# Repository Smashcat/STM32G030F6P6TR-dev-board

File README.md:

# STM32G030F6P6TR development board
Small breadboard friendly development board for the 32bit STM32G030F6P6TR microcontroller (currently stocked and priced at just over $1 on JLC!) with the following available features:

- 32Kb Flash
- 8Kb RAM.
- 12 bit ADC (16 channels)
- 2 x USART
- 2 x i2C
- i2S
- 2 x SPI
- 17 x GPIOs
- 5 DMA channels for above peripherals, plus memory to memory transfers
- Realtime clock with calendar and alarm with interrupt generation
- 8 x timers
- 2 x watchdogs

Note that many of the peripherals share pins.

This board includes 8 USER LEDs, 2 user buttons, UART to USB bridge, SHT30-DIS-B temperature and humidity sensor and all pins broken out for development use. Pullups on i2C pins. On-board 3.3V regulator from USB supply, with header pins for 3.3V and 5V available for use.

The V1.1 version also includes a LSM6DS3TR IMU device on the i2C bus. Other than this, it is identical.

All files required for full PCBA production at JLCPCB are included in the "Production files" folder.

Example firmware added to show use of i2C sensor, plus LEDs and internal clock.

V1.0

V1.1 (with IMU)

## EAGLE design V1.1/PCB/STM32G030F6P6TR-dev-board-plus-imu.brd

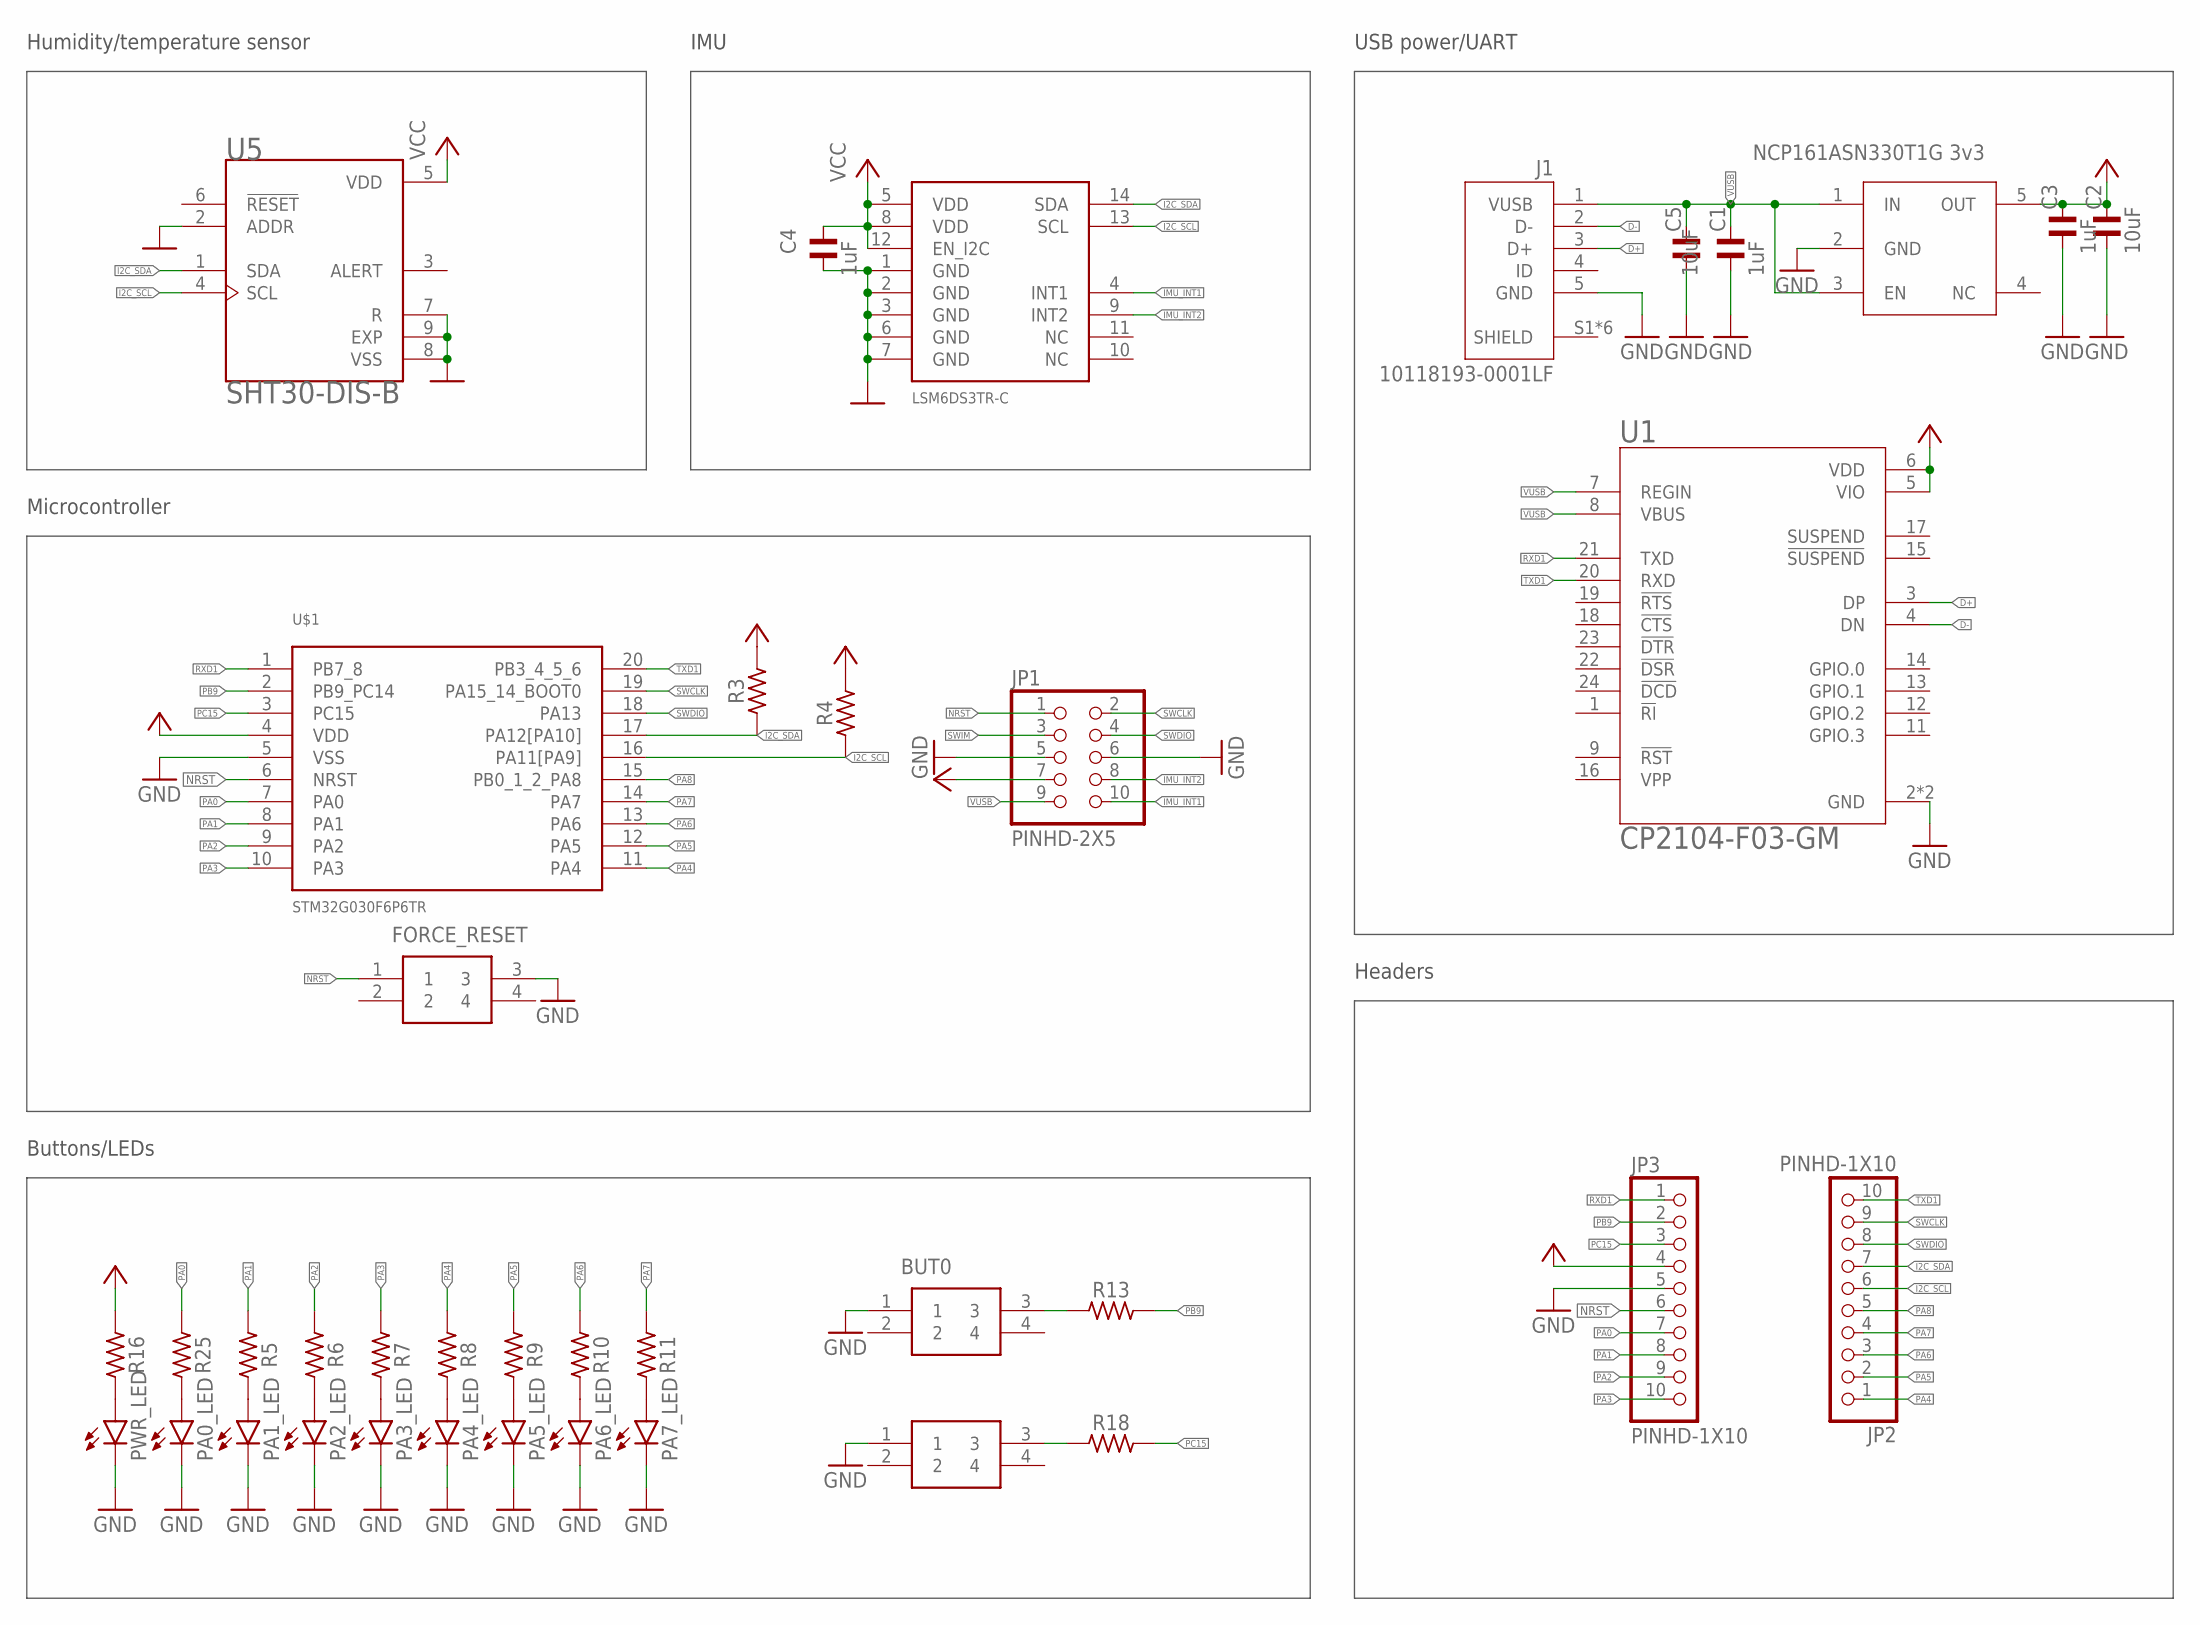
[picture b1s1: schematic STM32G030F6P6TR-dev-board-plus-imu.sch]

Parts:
3V3_REG1: 3V3; NCP718BSN330T1G
BUT0, BUT1: PTS645SM43SMTR92LFS; PTS645(SMT)
C1, C3, C4: 1uF; RC-MASTER-SMD_C0603MP
C2, C5: 10uF; RC-MASTER-SMD_C0603MP
FORCE_RESET: PTS645SM43SMTR92LFS; PTS645(SMT)
J1: 10118193-0001LF; FCI_10118193-0001LF
JP1: PINHD-2X5; 2X05
JP2, JP3: PINHD-1X10; 1X10
PA0_LED, PA1_LED, PA2_LED, PA3_LED, PA4_LED, PA5_LED, PA6_LED, PA7_LED: 20mA; CHIP-LED0603
PWR_LED: 20mA; CHIP-LED0603
R3, R4: 3k3; 52101-101-REV-A_RC-MASTER-SMD_R0603MP
R5, R6, R7, R8, R9, R10, R11, R16, R25: 1K; 52101-101-REV-A_RC-MASTER-SMD_R0603MP
R13, R18: 100R; 52101-101-REV-A_RC-MASTER-SMD_R0603MP
U1: CP2104-F03-GM; QFN50P400X400X80-25N
U5: SHT30-DIS-B; DFN250X250X100-9N
U$1: STM32G030F6P6TR; SOP65P640X120-20N
U$2: LSM6DS3TR-IMU; LSM6DS3TR

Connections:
D+: J1.3 (D+), U1.3 (DP)
D-: J1.2 (D-), U1.4 (DN)
GND: 3V3_REG1.2 (GND), BUT0.1, BUT1.1, C1.1, C2.1, C3.1, C4.1, C5.1, FORCE_RESET.3, J1.5 (GND), JP1.5, JP1.6, JP3.5, PA0_LED.C, PA1_LED.C, PA2_LED.C, PA3_LED.C, PA4_LED.C, PA5_LED.C, PA6_LED.C, PA7_LED.C, PWR_LED.C, U1.2 (GND), U1.25 (GND), U5.2 (ADDR), U5.7 (R), U5.8 (VSS), U5.9 (EXP), U$1.5 (VSS), U$2.1 (GND), U$2.2 (GND), U$2.3 (GND), U$2.6 (GND), U$2.7 (GND)
I2C_SCL: JP2.6, R4.2, U5.4 (SCL), U$1.16 (PA11[PA9]), U$2.13 (SCL)
I2C_SDA: JP2.7, R3.2, U5.1 (SDA), U$1.17 (PA12[PA10]), U$2.14 (SDA)
IMU_INT1: JP1.10, U$2.4 (INT1)
IMU_INT2: JP1.8, U$2.9 (INT2)
unnamed: PA1_LED.A, R5.1
unnamed: PA2_LED.A, R6.1
unnamed: PA0_LED.A, R25.1
unnamed: PA3_LED.A, R7.1
unnamed: PA4_LED.A, R8.1
unnamed: PA5_LED.A, R9.1
unnamed: PA6_LED.A, R10.1
unnamed: PA7_LED.A, R11.1
unnamed: BUT0.3, R13.2
unnamed: PWR_LED.A, R16.1
unnamed: BUT1.3, R18.2
NRST: FORCE_RESET.1, JP1.1, JP3.6, U$1.6 (NRST)
PA0: JP3.7, R25.2, U$1.7 (PA0)
PA1: JP3.8, R5.2, U$1.8 (PA1)
PA2: JP3.9, R6.2, U$1.9 (PA2)
PA3: JP3.10, R7.2, U$1.10 (PA3)
PA4: JP2.1, R8.2, U$1.11 (PA4)
PA5: JP2.2, R9.2, U$1.12 (PA5)
PA6: JP2.3, R10.2, U$1.13 (PA6)
PA7: JP2.4, R11.2, U$1.14 (PA7)
PA8: JP2.5, U$1.15 (PB0_1_2_PA8)
PB9: JP3.2, R13.1, U$1.2 (PB9_PC14)
PC15: JP3.3, R18.1, U$1.3 (PC15)
RXD1: JP3.1, U1.21 (TXD), U$1.1 (PB7_8)
SWCLK: JP1.2, JP2.9, U$1.19 (PA15_14_BOOT0)
SWDIO: JP1.4, JP2.8, U$1.18 (PA13)
SWIM: JP1.3
TXD1: JP2.10, U1.20 (RXD), U$1.20 (PB3_4_5_6)
VCC: 3V3_REG1.5 (OUT), C2.2, C3.2, C4.2, JP1.7, JP3.4, R3.1, R4.1, R16.2, U1.5 (VIO), U1.6 (VDD), U5.5 (VDD), U$1.4 (VDD), U$2.5 (VDD), U$2.8 (VDD), U$2.12 (EN_I2C)
VUSB: 3V3_REG1.1 (IN), 3V3_REG1.3 (EN), C1.2, C5.2, J1.1 (VUSB), JP1.9, U1.7 (REGIN), U1.8 (VBUS)

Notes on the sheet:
Humidity/temperature sensor
NCP161ASN330T1G 3v3
USB power/UART
Microcontroller
Buttons/LEDs
Headers
IMU

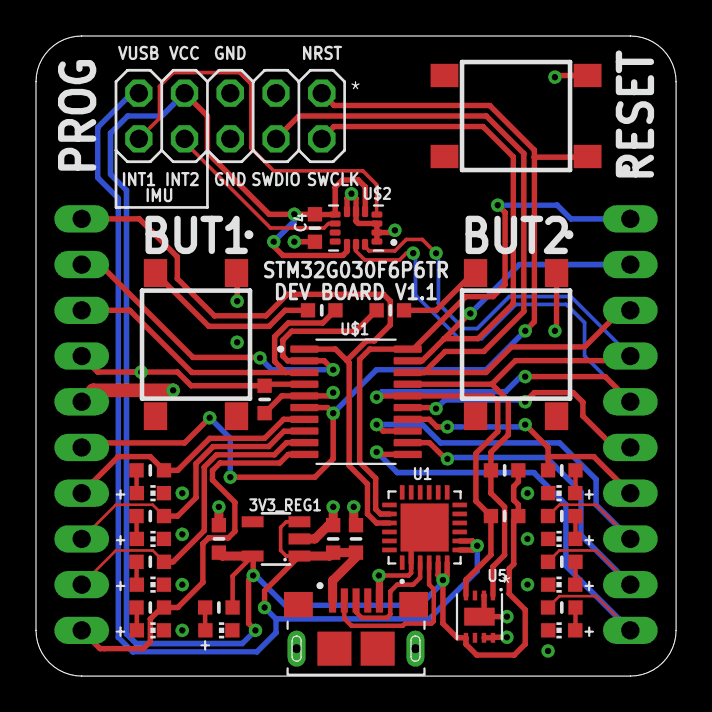
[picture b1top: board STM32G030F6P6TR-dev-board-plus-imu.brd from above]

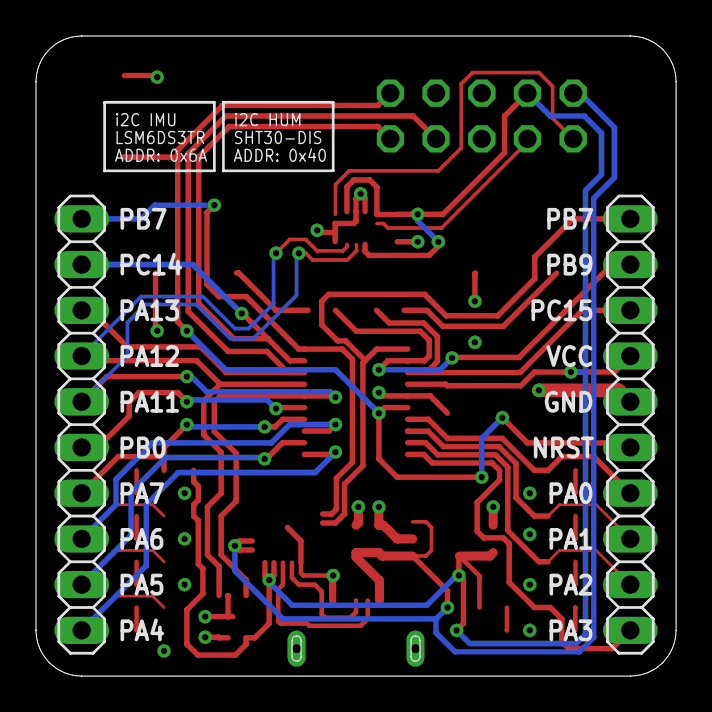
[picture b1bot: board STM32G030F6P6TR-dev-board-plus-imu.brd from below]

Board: 2 copper layers, 35.6 x 35.6 mm, 39 parts (2 on the bottom side), 36 nets.

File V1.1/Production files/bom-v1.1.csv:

Qty,Designator,Footprint,Comment,LCSC Part #,Description,Device
2,"R13, R18",52101-101-REV-A_RC-MASTER-SMD_R0603MP,100R,C22775,RESISTOR,52101-101-REV-A_RC-MASTER-SMD_R_0603MP
1,J1,FCI_10118193-0001LF,10118193-0001LF,C132562,Micro USB B Type Receptacle Check prices,10118193-0001LF
2,"C2, C5",RC-MASTER-SMD_C0603MP,10uF,C96446,NON-POLARIZED CAP,RC-MASTER-SMD_C_0603MP
9,"R5, R6, R7, R8, R9, R10, R11, R16, R25",52101-101-REV-A_RC-MASTER-SMD_R0603MP,1K,C21190 ,RESISTOR,52101-101-REV-A_RC-MASTER-SMD_R_0603MP
3,"C1, C3, C4",RC-MASTER-SMD_C0603MP,1uF,C15849,NON-POLARIZED CAP,RC-MASTER-SMD_C_0603MP
9,"PA0_LED, PA1_LED, PA2_LED, PA3_LED, PA4_LED, PA5_LED, PA6_LED, PA7_LED, PWR_LED",CHIP-LED0603,20mA,C434421,LED,LEDCHIP-LED0603
1,3V3_REG1,NCP718BSN330T1G,3V3,C587158,,NCP718BSN330T1G
2,"R3, R4",52101-101-REV-A_RC-MASTER-SMD_R0603MP,3k3,C22978,RESISTOR,52101-101-REV-A_RC-MASTER-SMD_R_0603MP
1,U1,QFN50P400X400X80-25N,CP2104-F03-GM,C47742,Silabs CP2104 USB to UART Bridge,CP2104-F03-GM
1,U$2,LSM6DS3TR,LSM6DS3TR-IMU,C967633,,LSM6DS3TR-IMU
1,JP1,2X05,PINHD-2X5,C225520,PIN HEADER,PINHD-2X5
3,"BUT0, BUT1, FORCE_RESET",PTS645(SMT),PTS645SM43SMTR92LFS,C127509,"C & K COMPONENTS - PTS645SM43SMTR92LFS - SWITCH, SPST, 0.05A, 12VDC, SMD, 4.3MM",PTS645SM43SMTR92LFS
1,U5,DFN250X250X100-9N,SHT30-DIS-B,C2687423,SHT3x Series 5.5 V ±3 %RH 0 to 100% Temperature and Humidity Sensor - DFN-8 Check availability,SHT30-DIS-B
1,U$1,SOP65P640X120-20N,STM32G030F6P6TR,C529330,,STM32G030F6P6TR

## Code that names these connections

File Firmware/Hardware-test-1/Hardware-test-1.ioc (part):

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Mcu.Name=STM32G030F6Px
Mcu.Package=TSSOP20
Mcu.UserName=STM32G030F6Px
PA0.GPIOParameters=PinState,GPIO_Label
PA0.GPIO_Label=out0
PA0.PinState=GPIO_PIN_SET
PA0.Signal=GPIO_Output
PA1.GPIOParameters=PinState,GPIO_Label
PA1.GPIO_Label=out1
PA1.PinState=GPIO_PIN_SET
PA1.Signal=GPIO_Output
PA11\ [PA9].Mode=I2C
PA11\ [PA9].Signal=I2C2_SCL
PA12\ [PA10].Mode=I2C
PA12\ [PA10].Signal=I2C2_SDA
PA13.Mode=Serial_Wire
PA13.Signal=SYS_SWDIO
PA14-BOOT0.Mode=Serial_Wire
PA14-BOOT0.Signal=SYS_SWCLK
PA2.GPIOParameters=PinState,GPIO_Label
PA2.GPIO_Label=out2
PA2.PinState=GPIO_PIN_SET
PA2.Signal=GPIO_Output
PA3.GPIOParameters=PinState,GPIO_Label
PA3.GPIO_Label=out3
PA3.PinState=GPIO_PIN_SET
PA3.Signal=GPIO_Output
PA4.GPIOParameters=PinState,GPIO_Label
PA4.GPIO_Label=out4
PA4.PinState=GPIO_PIN_SET
PA4.Signal=GPIO_Output
PA5.GPIOParameters=PinState,GPIO_Label
PA5.GPIO_Label=out5
PA5.PinState=GPIO_PIN_SET
PA5.Signal=GPIO_Output
PA6.GPIOParameters=PinState,GPIO_Label
PA6.GPIO_Label=out6
PA6.PinState=GPIO_PIN_SET
PA6.Signal=GPIO_Output
PA7.GPIOParameters=PinState,GPIO_Label
PA7.GPIO_Label=out7
PA7.PinState=GPIO_PIN_SET
PA7.Signal=GPIO_Output
PA8.GPIOParameters=PinState,GPIO_Label
PA8.GPIO_Label=SIM_KEY_OUT
PA8.PinState=GPIO_PIN_SET
PA8.Signal=GPIO_Output
PB6.Mode=Asynchronous
PB6.Signal=USART1_TX
PB7.Mode=Asynchronous
PB7.Signal=USART1_RX
PC14-OSC32_IN\ (PC14).GPIOParameters=GPIO_PuPd,GPIO_Label
PC14-OSC32_IN\ (PC14).GPIO_Label=but2
PC14-OSC32_IN\ (PC14).GPIO_PuPd=GPIO_PULLUP
PC14-OSC32_IN\ (PC14).Signal=GPIO_Input
PC15-OSC32_OUT\ (PC15).GPIOParameters=GPIO_PuPd,GPIO_Label
PC15-OSC32_OUT\ (PC15).GPIO_Label=but1
PC15-OSC32_OUT\ (PC15).GPIO_PuPd=GPIO_PULLUP
PC15-OSC32_OUT\ (PC15).Signal=GPIO_Input
RCC.HSE_VALUE=8000000
RCC.SYSCLKFreq_VALUE=16000000
board=custom

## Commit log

2022-04-10 Fixed folder name
2022-04-10 Updated render, revered mounting headers
2022-04-12 Updated board layout by reversing pin header to bottom side. Added datasheet for MCU
2022-04-13 Added IMU version (1.1)
2022-04-13 Updated main README
2022-06-03 Added example firmware
2022-06-03 Deleted old directories
2022-06-05 Slight change to LED animation
